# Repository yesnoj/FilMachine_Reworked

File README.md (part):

# FilMachine — Automated Film Development Machine

FilMachine is an automated film processing machine designed for photographic film development. It handles the entire process: chemical baths, water rinses, temperature regulation, and motor-driven film agitation — all controlled through a 4.3" color touchscreen display.

The project includes a **desktop simulator** (SDL2 + LVGL) that reproduces the full touchscreen UI on macOS/Linux (a Windows build is produced by CI), enabling rapid development and testing without physical hardware, plus an **automated test suite** (19 suites). A **Flutter companion app** connects via WebSocket and provides full remote control from any mobile device on the same network.

The interface is **bilingual (English / Italiano)** — selectable from Settings, applied with an automatic reboot — and every boot writes a **diagnostic log to the SD card** (`/log/boot_NNNN.txt`), including the crash summary of the previous run when the firmware panicked.

The repository also holds the mechanical side of the project: the 3D-printed **film reel auto-loader** (bench prototype v1, for 135 and 120 film) — see [Film Reel Auto-Loader](#film-reel-auto-loader-3d-printed-prototype).

---

## Table of Contents

1. [What is FilMachine?](#what-is-filmachine)
2. [Project Architecture](#project-architecture)
3. [Directory Structure](#directory-structure)
4. [Building the Project](#building-the-project)
5. [Running the Simulator](#running-the-simulator)
6. [Running the Tests](#running-the-tests)
7. [WebSocket Server & Remote Control](#websocket-server--remote-control)
8. [Flutter Companion App](#flutter-companion-app)
9. [User Interface Guide](#user-interface-guide)
10. [Firmware Update (OTA)](#firmware-update-ota)
11. [Hardware Specifications](#hardware-specifications)
12. [Bill of Materials (Components)](#bill-of-materials-components)
13. [Film Reel Auto-Loader (3D-Printed Prototype)](#film-reel-auto-loader-3d-printed-prototype)
14. [Diagnostics & Bring-up Page](#diagnostics--bring-up-page)
15. [Build-time Switches](#build-time-switches)
16. [Configuration & Persistence](#configuration--persistence)
17. [Language / Localization](#language--localization)
18. [SD Boot & Crash Log](#sd-boot--crash-log)
19. [Typical Workflows](#typical-workflows)
20. [Developer Quick Reference](#developer-quick-reference)
21. [Authors](#authors)

---

## What is FilMachine?

FilMachine takes the guesswork out of developing photographic film at home or in a small lab. Instead of manually timing each step, pouring chemicals by hand, and constantly checking the thermometer, FilMachine automates everything. You load your film in the developing tank, select a process, and press Start. The machine takes care of the rest: filling the right chemical at the right time, keeping the temperature stable, rotating the film at the correct speed, rinsing between steps, and alerting you when the process is complete.

It supports both **color negative** (C41, E6) and **black & white** film development workflows, with full customization of every parameter.

---

## Project Architecture

The project has a **dual-target build system** that produces ESP32-P4 firmware or a native desktop application from the same codebase. The only supported hardware board is the **Guition JC4880P433** (ESP32-P4).

### Technology Stack

| Layer | Firmware (ESP32-P4) | Simulator (macOS/Linux) |
|-------|-------------------|------------------------|
| **UI Library** | LVGL 9.5.0 | LVGL 9.5.0 (identical) |
| **Display** | ST7701S 480×800 MIPI-DSI → landscape 800×480 via PPA | SDL2 window (800×480) |
| **Touch Input** | GT911 (physical 480×800 → remapped to 800×480) | SDL2 mouse events |
| **Storage** | FatFS on MicroSD (SDMMC 4-bit, ~40 MB/s) | POSIX file I/O (sd/ directory) |
| **RTOS** | FreeRTOS (ESP-IDF) | Stub (queues work, tasks are no-ops) |
| **2D Acceleration** | PPA hardware engine (rotate, scale, blend, fill) | — |
| **Audio** | ES8311 codec via I2S + power amplifier | — |
| **Temp Sensors** | DS18B20 OneWire | Simulated (20°C ambient, heater model) |
| **Motor/Pump** | DBH-12V dual H-bridge (motor ch.A + pump ch.B) + MCP23017 solenoid driver | printf stubs |
| **OTA Updates** | esp_ota_ops + esp_http_server | Simulated (progress timer) |
| **Build Tool** | ESP-IDF (`idf.py`) | CMake + Make |
| **Sensors** | Flow meter, water level, hall effect | Simulated |
| **Compiler** | riscv32-esp-elf-gcc | Native cc/gcc/clang |

### How the Simulator Works

The simulator replaces all hardware-specific code with a **stub layer** that provides compatible implementations:

- **FatFS stubs** map firmware paths (e.g., `/FilMachine.json`) to files inside an `sd/` subdirectory of the directory the simulator is launched from, so read/write operations work transparently.
- **FreeRTOS stubs** provide working queue implementations (xQueueCreate, xQueueSend, xQueueReceive) using simple circular buffers. Task creation is a no-op since there are no real threads — instead, the main loop drains the system queue every frame.
- **Hardware stubs** (GPIO, I2C, SPI, solenoid driver, motor, temperature) are either no-ops or printf-based logging functions. Temperature readings come from a simple thermal model that simulates heating/cooling.
- **OTA stubs** simulate the firmware update flow with a progress timer (0→100%) and fake IP address, allowing full UI testing without real hardware.
- **LVGL's SDL2 driver** provides the display backend and mouse input, which simulates the capacitive touchscreen.

The key architectural principle is that **all UI code is shared 1:1** between firmware and simulator. Pages, elements, event handlers, and business logic are identical — only the hardware abstraction layer changes.

---

## Directory Structure

```
FilMachine_Reworked/
│
├── main/                          # Core source (shared with ESP32 firmware)
│   ├── include/
│   │   └── FilMachine.h           #   Main header — all structs, enums, constants, prototypes
│   ├── FilMachine.c               #   ESP32 entry point — board-conditional display/touch init
│   ├── accessories.c              #   Utilities — linked lists, deep copy, config I/O, keyboard
│   ├── lang.c                     #   EN/IT string table (generated by scripts/gen_lang.py)
│   ├── sd_log.c                   #   Boot/crash logger on SD (/log/boot_NNNN.txt, firmware only)
│   ├── mini_json.c                #   Dependency-free JSON parser for the config file
│   ├── ota_update.c               #   OTA firmware update (SD card + Wi-Fi web server)
│   ├── ws_server.c                #   WebSocket server for Flutter companion app
│   ├── film_loader.c              #   Film loading cycle (wind, stall detect, cut, tail) — Tools → Load film
│   └── ui_profile.c               #   Centralized UI layout constants (800×480)
│
├── c_pages/                       # UI pages (screens)
│   ├── page_splash.c              #   Splash screen — standard, random, and custom modes with
│   │                              #     10 palettes, 6 shape styles, 9 title fonts, PRNG engine
│   ├── page_menu.c                #   Tab bar navigation (Processes / Settings / Tools)
│   ├── page_processes.c           #   Process list with filtering
│   ├── page_processDetail.c       #   Process creation & editing
│   ├── page_stepDetail.c          #   Step creation & editing with validation
│   ├── page_settings.c            #   Machine settings, grouped in sections (process, rotation, liquids, display, system)
│   ├── page_tools.c               #   Maintenance tools, import/export, statistics, OTA
│   ├── page_checkup.c             #   Process execution — the most complex page
│   └── page_debug.c               #   Hidden diagnostics / bring-up page (live sensors, output tests)
│
├── c_elements/                    # Reusable UI components
│   ├── element_process.c          #   Process list item (drag, delete, duplicate)
│   ├── element_step.c             #   Step list item (swipe gestures, edit/delete)
│   ├── element_filterPopup.c      #   Filter dialog (name, type, preferred)
│   ├── element_messagePopup.c     #   Generic confirmation/alert popups
│   ├── element_rollerPopup.c      #   Numeric selector (roller) widget
│   ├── element_calibPopup.c       #   Dual temperature calibration popup (bath + chemistry offsets)
│   ├── element_speedPopup.c       #   Pump / motor speed tuning popup with live test
│   ├── element_fillPopup.c        #   Maintenance "Fill bath" popup (auto-stop on level, flow or timeout)
│   ├── element_loadPopup.c        #   Film loading popup (135/120, progress, Cut now, blade test)
│   ├── element_cleanPopup.c       #   Cleaning process UI with timer
│   ├── element_drainPopup.c       #   Drain process UI with animated tank bars
│   ├── element_splashPopup.c      #   Splash screen config popup with live preview
│   ├── element_selfcheckPopup.c   #   Self-check diagnostic wizard (8-phase hardware test)
│   ├── element_otaWifiPopup.c     #   Wi-Fi OTA update popup (IP + PIN + progress)
│   └── element_wifiPopup.c       #   Wi-Fi connection popup (scan, connect, status)
│
├── c_fonts/                       # Custom icon fonts (7 sizes: 15/20/30/40/50/60/100px)
│   │                              #   + 8 custom splash title fonts (48px) + Montserrat 64
├── drivers/                       # Custom peripheral drivers (ESP-IDF compatible)
│   ├── include/                   #   Driver headers (mcp23017.h, ds18b20.h, sensors.h, audio.h, servo.h)
│   ├── mcp23017.c                 #   I2C 16-bit I/O expander (Adafruit solenoid driver)
│   ├── ds18b20.c                  #   OneWire temperature sensor (shared bus)
│   ├── audio.c                    #   ES8311 codec bring-up + tone/volume (board only)
│   ├── servo.c                    #   Cutter servo, LEDC 50 Hz PWM on GPIO 28 (board only)
│   └── sensors.c                  #   Flow meter, water level, hall effect sensors (+ reel pulse counter)
│
├── components/                    # ESP32-P4 specific hardware drivers
│   ├── st7701_lcd/                #   ST7701S MIPI-DSI LCD driver (480×800)
│   ├── ppa_engine/                #   PPA hardware 2D accelerator (rotate, scale, fill, blend)
│   ├── driver/                    #   ESP-IDF driver compatibility shims
│   └── espressif__esp_lcd_touch/  #   Touch panel abstraction layer
│
├── src/
│   └── main.c                     # Simulator entry point (SDL2 display, main loop,
│                                  #   demo data generator, system queue drain)
│
├── stub/                          # Hardware abstraction for simulator
│   ├── esp_stubs.h/c              #   ESP32 GPIO, timer, heap stubs
│   ├── fatfs_stubs.h/c            #   FatFS → POSIX filesystem mapping
│   ├── freertos_stubs.h/c         #   Queue stubs (circular buffer), task stubs (no-op)
│   ├── driver/                    #   GPIO, I2C, LEDC, SDMMC driver stubs
│   └── (redirect headers)         #   Thin #include wrappers for ESP-IDF compatibility
│
├── tests/                         # Automated test suite
│   ├── test_runner.h/c            #   Test framework & entry point
│   ├── test_helpers.c             #   Touch input simulation
│   ├── test_navigation.c          #   Splash, menu, tab switching
│   ├── test_processes.c           #   Process list display & creation
│   ├── test_process_crud.c        #   Process create/read/update/delete
│   ├── test_steps.c               #   Step creation, swipe, deletion
│   ├── test_step_crud.c           #   Step lifecycle
│   ├── test_execution.c           #   Process checkup execution flow
│   ├── test_persistence.c         #   Config save/load/restore
│   ├── test_settings.c            #   Settings UI & validation
│   ├── test_filter.c              #   Filter logic
│   ├── test_tools.c               #   Maintenance tools
│   ├── test_edge_cases.c          #   Boundary conditions & error paths
│   ├── test_utilities.c           #   Helper function tests
│   ├── test_ota.c                 #   OTA update UI & Wi-Fi popup tests
│   ├── test_websocket.c           #   WebSocket command tests
│   ├── test_new_settings.c        #   Extended settings tests
│   ├── test_selfcheck.c           #   Self-check wizard tests
│   ├── test_live_sync.c           #   Live sync integration tests
│   ├── test_ui_profile.c          #   UI profile validation & sensor stubs
│   ├── test_film_loader.c         #   Film loader state machine, safety checks, popup
│   ├── test_maintenance_remote.c  #   Drain / Clean / Export driven by WebSocket commands
│   └── test_destroy_and_lifecycle.c # Memory cleanup & object destruction
│
├── lvgl/                          # LVGL 9.5.0 library (auto-cloned on first build, gitignored)
├── lvgl_config/
│   └── lv_conf.h                  # LVGL configuration (RGB565, C-library malloc as on the board, dark theme)
│
├── boards/                        # Board-specific hardware definitions
│   ├── board.h                    #   Board selector (includes correct board header)
│   ├── board_jc4880p433.h         #   JC4880P433 pin assignments, peripherals, H-bridge config
│   └── board_simulator.h          #   Simulator stubs (matching pin constants)
│
├── scripts/
│   ├── genFilMachineCFG.py        # SD config generator (FilMachine.json with realistic film recipes)
│   ├── gen_lang.py                # EN/IT string table generator (holds the Italian dictionary)
│   └── bump_version.sh            # Increments the BUILD field of version.txt
│
├── hardware/
│   └── FilMachine_Breakout_v1/    # KiCad project + BOM: breakout board for the Expand IO header
│
├── 3D_Models/
│   └── FilMachine_caricatore_v1/  # 3D-printed film reel auto-loader: STEP, STL, previews,
│                                  #   CadQuery source and its own README (in Italian)
│
├── docs/
│   └── hardware_architecture.svg  # System architecture diagram (shown under Hardware Specifications)
├── tools/
│   └── lvgl_splash_generator.jsx  # Splash-screen generator (React component that emits LVGL C code)
├── data/                          # Sample SD config files (FilMachine.json + legacy .cfg), not used by the build
├── .github/workflows/
│   └── windows-sim.yml            # CI: builds the simulator for Windows (MSYS2/MinGW)
│
├── CMakeLists.txt                 # Dual-target build (ESP-IDF P4 + simulator/tests)
├── version.txt                    # Firmware version, MAJOR.MINOR.PATCH.BUILD (single source of truth)
├── partitions.csv                 # Custom OTA partition table (16 MB flash)
├── sdkconfig.defaults             # ESP-IDF shared defaults
├── sdkconfig.defaults.esp32p4     # ESP-IDF defaults for ESP32-P4 target
├── flash_p4.sh                    # All-in-one build + flash + monitor for the ESP32-P4 board (macOS)
├── ui_debug_registry.inc          # Widget-name registry for the simulator's F2 debug overlay
├── COMMANDS.md                    # Quick command reference (in Italian)
├── AUDIT_REPORT.md                # Firmware/app audit of 6 July 2026 (firmware v0.0.0.50)
├── FilMachine_Custom_PCB_BOM.xlsx # Design worksheet for a custom PCB: BOM, pin maps, power budget (in Italian)
├── DistintaComponenti.xlsx        # Parts list with specs, quantities, prices and links (in Italian)
├── MDC_db.csv                     # Film/developer development-time table (9,142 rows; not read by the firmware yet)
├── setup.sh                       # Legacy: one-off script that built the old Simulator_v2 folder (not needed)
└── flash.sh                       # Legacy: ESP32-S3 flash through the old FilMachine_Pete repo (not for the P4)
```

---

## Building the Project

### Prerequisites

**macOS:**
```bash
brew install cmake sdl2 pkg-config
```

**Ubuntu / Debian:**
```bash
sudo apt install cmake libsdl2-dev pkg-config build-essential
```

LVGL v9.5.0 is automatically cloned from GitHub on the first build if not present (the firmware pulls the same version through the ESP-IDF component manager, `lvgl/lvgl ~9.5.0`).

**Windows:** there is no local recipe; the GitHub Actions workflow `.github/workflows/windows-sim.yml` builds `filmachine_sim.exe` with MSYS2/MinGW on every push to `main` that changes more than the documentation (or on demand from the Actions tab) and uploads it — with its runtime DLLs and a freshly generated `sd/` config — as the `filmachine-sim-windows` artifact.

### Build the Simulator

```bash
mkdir -p build800 && cd build800
cmake ..
make filmachine_sim
```

The simulator opens an 800×480 window matching the JC4880P433 physical panel in landscape orientation.

### Build the Tests

```bash
mkdir -p build800 && cd build800
cmake ..
make filmachine_test
./filmachine_test
```

### Build the Firmware

Requires the [ESP-IDF](https://docs.espressif.com/projects/esp-idf/en/latest/) toolchain (**v5.5.x** or later) installed and configured.

**Important:** run `idf.py` from the **project root**, not from `build800/`.

```bash
cd FilMachine_Reworked
. $HOME/esp/esp-idf-v5.5/export.sh     # Must be ESP-IDF 5.5.x or later

# First-time setup: set target to esp32p4 (creates sdkconfig from defaults)
idf.py set-target esp32p4

# Build — board is auto-detected from IDF_TARGET
idf.py build
```

The `main/CMakeLists.txt` automatically sets `-DBOARD_JC4880P433`. No manual `-DCMAKE_C_FLAGS` flag is needed (passing `-D CMAKE_C_FLAGS="-DBOARD_JC4880P433"` is harmless but redundant).

> **See [`COMMANDS.md`](COMMANDS.md)** for the canonical quick reference: simulator + board build, flash/monitor, generating and copying the SD config, version bumping and cleanup.

#### Flash and monitor

The firmware binary is produced at `build/FilMachine.bin`. To flash it directly to a connected board:

```bash
idf.py flash
```

Or use the all-in-one helper (written for macOS), which sets the target if needed, patches `sdkconfig` for the P4 board, increments the build number in `version.txt`, builds, looks for the serial port, flashes and opens the monitor:
```bash
./flash_p4.sh
```

> `flash.sh` and `setup.sh` are leftovers of the earlier ESP32-S3 workflow (they copy sources between the old `FilMachine_Simulator_v2` folder and the `FilMachine_Pete` repository). They are not used for the ESP32-P4 and can be ignored.

**P4 note:** the bootloader offset on ESP32-P4 is `0x2000` (different from ESP32-S3's `0x0`). This is handled automatically by `idf.py` when the target is set correctly.

To check the firmware size (useful for verifying OTA partition fit):
```bash
idf.py size
```

---

## Running the Simulator

### Simulator UI debug overlay

The simulator includes a built-in UI inspection mode to speed up layout tuning.

- Press **F2** to enable or disable the overlay.
- When enabled, moving the mouse over the UI shows:
  - the resolved component name when available (for example `gui.page.processes.newProcessButton`)
  - the object position (`x`, `y`)
  - the object size (`w`, `h`)
- While the overlay is enabled, **right click** dumps the hovered object to the terminal/console.

This is especially useful when adjusting coordinates inside `ui_profile.c`, because you can identify the exact widget and immediately see its current geometry in the simulator.

```bash
cd build800
./filmachine_sim
```

The simulator opens an 800×480 window that reproduces the exact touchscreen interface. Use the mouse to simulate touch input (click = tap, click-drag = swipe/scroll).

### What works in the simulator

- Full UI navigation (all pages, popups, dialogs)
- Splash screen with live preview popup, 10 palettes, 6 shape styles, 9 custom fonts
- Process creation, editing, duplication, deletion
- Step management with swipe gestures
- Settings with slider/switch/radio controls
- Filter and search functionality
- Configuration save/load (reads/writes `sd/FilMachine.json`)
- Export/Import (backup to `sd/FilMachine_Backup.json`)
- Drain machine with animated tank-level bars and relay management
- Empty chemistry (machine v7): C1, C2 or C3 into its recovery bottle through the pump and the recovery outlet, line washed before and after, with a source → tank → bottle animation
- Clean machine with per-container rinse cycles and arc progress
- Self-check diagnostic wizard with 8-phase hardware test simulation (temp sensors, pump, heater, valves, containers, motor)
- OTA update UI (SD card check + Wi-Fi popup with simulated IP/PIN/progress)
- Simulated temperature readings with heater model and calibration offset
- Persistent alarm sound (SDL audio 880Hz beep, repeats every 10s until dismissed)
- Drain/fill overlap processing (adjusts step timing based on overlap percentage)
- Machine statistics persistence (saved in config file, survives restart)
- Temperature sensor calibration (Tune button calculates and applies offset)
- Console logging of all system actions (`[SIM] sysAction: ...`)
- WebSocket server on port 81 for Flutter companion app remote control
- Full remote process start, stop, and checkup advance via WebSocket
- Remote CRUD for processes and steps (create, edit, delete from Flutter)

### What is simulated (no real hardware)

- Temperature sensors return simulated values (20°C ambient, gradual heating/cooling)
- Motor control outputs to console only
- Relay switching outputs to console only
- OTA writes to a fake partition (progress simulated, no actual flash)
- Wi-Fi connection is simulated (fake IP 192.168.1.42, no real server)
- Reboot is a no-op (prints message)

### Generating sample data

To generate realistic film development recipes:

```bash
python3 scripts/genFilMachineCFG.py --realistic --output build800/sd/
```

This creates config files with authentic C41, E6, and B&W development processes.

---

## Running the Tests

```bash
cd build800
./filmachine_test
```

Results are displayed in the terminal and saved to `test_results/test_results_YYYYMMDD_HHMMSS.txt`.

### Test Suites

| Suite | Description |
|-------|-------------|
| **Navigation** | Splash screen, menu display, tab switching |
| **Processes** | Process list rendering, creation UI |
| **Process CRUD** | Full create/read/update/delete lifecycle |
| **Steps** | Step creation, swipe gestures, deletion |
| **Step CRUD** | Step lifecycle with validation |
| **Execution** | Process checkup and execution flow |
| **Persistence** | Config save → reload → verify all fields, stats persistence, calibration offset |
| **Settings** | Settings UI, default values, slider/switch behavior, calibration, alarm |
| **Filter** | Filter by name, film type, preferred flag |
| **Tools** | Cleaning, draining, statistics display, timer pause/resume, alarm functions |
| **Edge Cases** | Boundary conditions, max limits, error recovery |
| **Utilities** | Helper functions, linked list operations, drain/fill overlap calculation |
| **UI Profile & Sensors** | Profile values match original, popup dimensions, font pointers, sensor stubs, board constants |
| **OTA** | OTA update UI, Wi-Fi popup PIN generation, progress popup |
| **WebSocket** | WebSocket command handling, async LVGL dispatch |
| **New Settings** | Extended settings validation |
| **Self-check** | Self-check diagnostic wizard phases |
| **LiveSync** | Live sync between WebSocket state and LVGL UI |
| **Destroy & Lifecycle** | Memory cleanup, object destruction |
| **Film loader** | Loading cycle 135/120, early stall / no spin / too long errors, Cut now, Stop, blade test, popup from the app |
| **Maintenance from the app** | Drain and Clean started, stopped and closed by WebSocket commands (popups on the display, state fields), only the selected containers cleaned, one tool at a time, no process while one runs, Export queued with its result in the state |

The persistence tests verify that every field (process name, temperature, tolerance, film type, preferred flag, step names, durations, types, sources, discard flags) survives a full save-and-reload cycle.

**Repeatable runs.** Every run starts from the same data: the runner generates three test processes with the default settings and rewrites `sd/FilMachine.json` in the run directory, so a run never depends on what the previous one saved (steps used to pile up on the first process until the 30-step limit made the step tests fail). `FM_TEST_ONLY=<suite>,<suite>` runs only some suites (names after `test_suite_`, e.g. `FM_TEST_ONLY=navigation,tools`).

**Timers run on real time.** The SDL display makes LVGL read the real clock, so `test_pump()` processes events but does not advance LVGL timers; tests that wait for a 1 s timer sleep (see `pump_real()` in `test_maintenance_remote.c`).

**Memory.** The simulator and the tests use the C-library `malloc` for LVGL, like the board. With LVGL's own 256 KB pool the heap fragmented after a few suites, an allocation failed and LVGL's malloc assert spun forever, which looked like random hangs in the step tests. To check memory errors, build the runner with `-fsanitize=address`: AddressSanitizer then sees LVGL's allocations too.

---

## WebSocket Server & Remote Control

The simulator and firmware include a built-in WebSocket server (`ws_server.c`) that enables remote control from the Flutter companion app or any WebSocket client. The server starts automatically and listens on **port 81** at path `/ws`.

### Supported Commands

All commands use JSON format: `{"cmd":"command_name", ...params}`.

| Command | Parameters | Description |
|---------|-----------|-------------|
| `get_state` | — | Returns full machine state (settings, runtime, temperatures, progress, alarms, maintenance fill, film loader, drain, clean and export status) |
| `get_processes` | — | Returns complete process list with steps, indexed for remote referencing |
| `start_process` | `index` | Start a process by list index; initializes checkup and begins execution |
| `checkup_advance` | — | Advance to next checkup phase (Setup → Fill → Temp → Check → Processing) |
| `stop_now` | — | Immediately halt the running process and drain |
| `stop_after` | — | Stop after the current step completes |
| `close_process` | — | Close a finished/stopped process and free checkup resources |
| `create_process` | `name, temp, tolerance, filmType, tempControlled, preferred` | Create a new process |
| `edit_process` | `index, name, temp, tolerance, filmType, tempControlled, preferred` | Edit an existing process |
| `delete_process` | `index` | Delete a process |
| `add_step` | `processIndex, name, mins, secs, type, source, discard` | Add a step to a process |
| `edit_step` | `processIndex, stepIndex, name, mins, secs, type, source, discard` | Edit a step |
| `delete_step` | `processIndex, stepIndex` | Delete a step |
| `reorder_step` | `processIndex, from, to` | Move a step within a process |
| `set_setting` | `key, value` | Update a machine setting (see key list below) |
| `reset_defaults` | — | Restore all settings to factory defaults |
| `wifi_scan` | — | Scan for Wi-Fi networks; results arrive via a `wifi_scan_results` event |
| `fill_start` / `fill_stop` | `target` (0 = water bath, 1 = chemistry) | Maintenance fill (self-calibrates the fill time; refused with `fill_rejected` while a process runs) |
| `tune_test` / `tune_set` / `tune_cancel` | `kind` (0 pump, 1 motor, 2 volume), `percent`, `on` | Live test, store or cancel a Tune value |
| `drain_start` / `drain_stop` / `drain_close` | — | Drain machine: start (no confirm page, the app asks), Stop, Close after the end (alarm off, popup closed). Refused with `drain_rejected` while a process or another maintenance tool runs |
| `recover_start` / `recover_stop` / `recover_close` | `container` (0 = C1, 1 = C2, 2 = C3) | Empty that chemistry into its recovery bottle (machine v7): wash the line, discard the head, transfer, wash again. Progress in `recoverToolState` (0 idle, 1 running, 2 stopping, 3 done, 4 stopped), `recoverToolPhase` (0..3), `recoverToolPct`, `recoverToolRemaining`, `recoverToolMovedMl`. Refused with `recover_rejected` while a process or another tool runs; a drain still finishing is waited for |
| `clean_start` | `mask` (bit0 C1, bit1 C2, bit2 C3), `cycles` (1–5), `drainWb` | Clean machine with these choices (shown on the display popup). Refused with `clean_rejected` (`processing`, `busy`, `no_container`) |
| `clean_stop` / `clean_close` | — | Clean: Stop (the container is pumped back first) / Close after the end |
| `export_config` | — | Export configuration and processes to the backup file on the SD card; the result arrives as `exportSeq` / `exportOk` in the state |
| `load_start` | `format` (0 = 135, 1 = 120) | Start loading the film onto the reel (refused with a `load_rejected` event while a process runs or a load is in progress) |
| `load_stop` | — | Stop the loading (motor off, blade back to rest) |
| `load_cut` | — | Cut now, without waiting for the reel to stop |
| `cutter_test` | `angle` (0–180) | Hold the cutter servo at that angle for a few seconds (setup) |
| `cutter_cycle` | — | One blade up/down cycle, motor off |

The `cleanTool*` state fields include `cleanToolProcessArc`, `cleanToolCycleArc` and `cleanToolPumpArc`: the values of the three arcs exactly as drawn on the display's Clean popup, so the app draws the same picture.

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
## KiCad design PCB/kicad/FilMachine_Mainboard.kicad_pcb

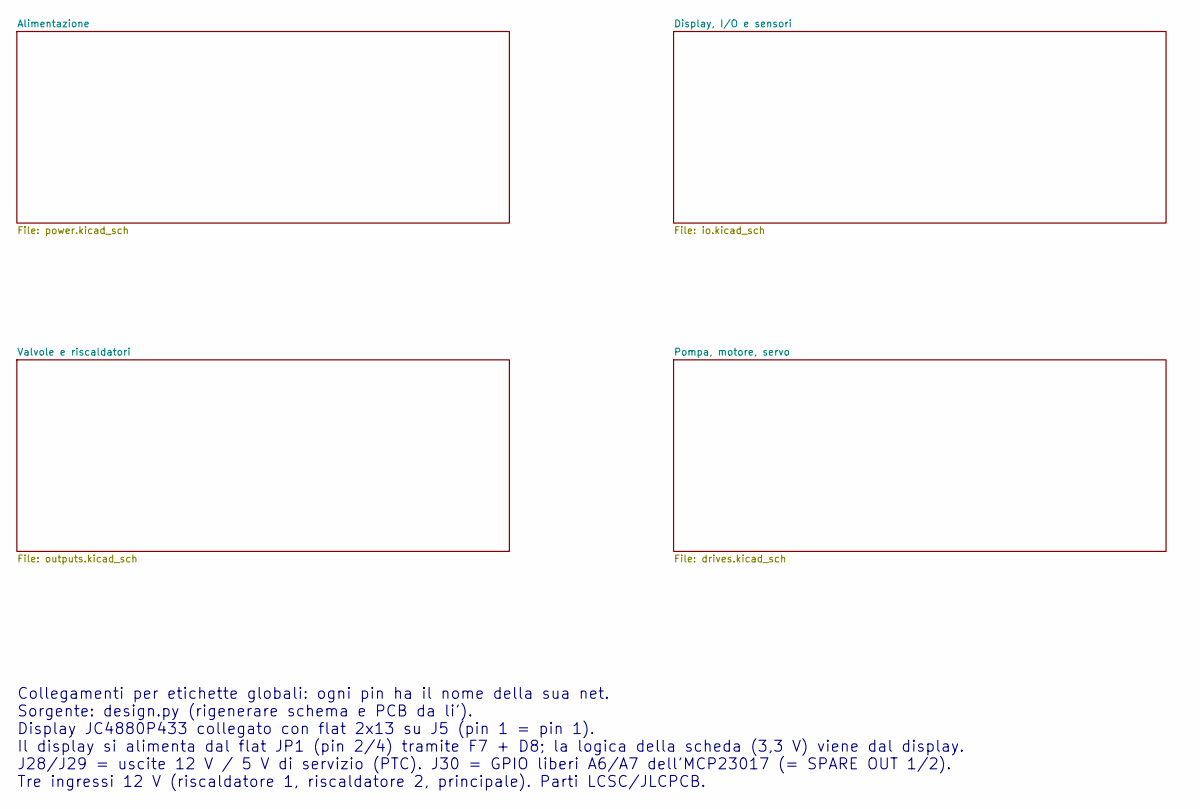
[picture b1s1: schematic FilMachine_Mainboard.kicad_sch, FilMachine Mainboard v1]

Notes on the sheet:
Collegamenti per etichette globali: ogni pin ha il nome della sua net. Sorgente: design.py (rigenerare schema e PCB da li'). Display JC4880P433 collegato con flat 2x13 su J5 (pin 1 = pin 1). Il display si alimenta dal flat JP1 (pin 2/4) tramite F7 + D8; la logica della scheda (3,3 V) viene dal disp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

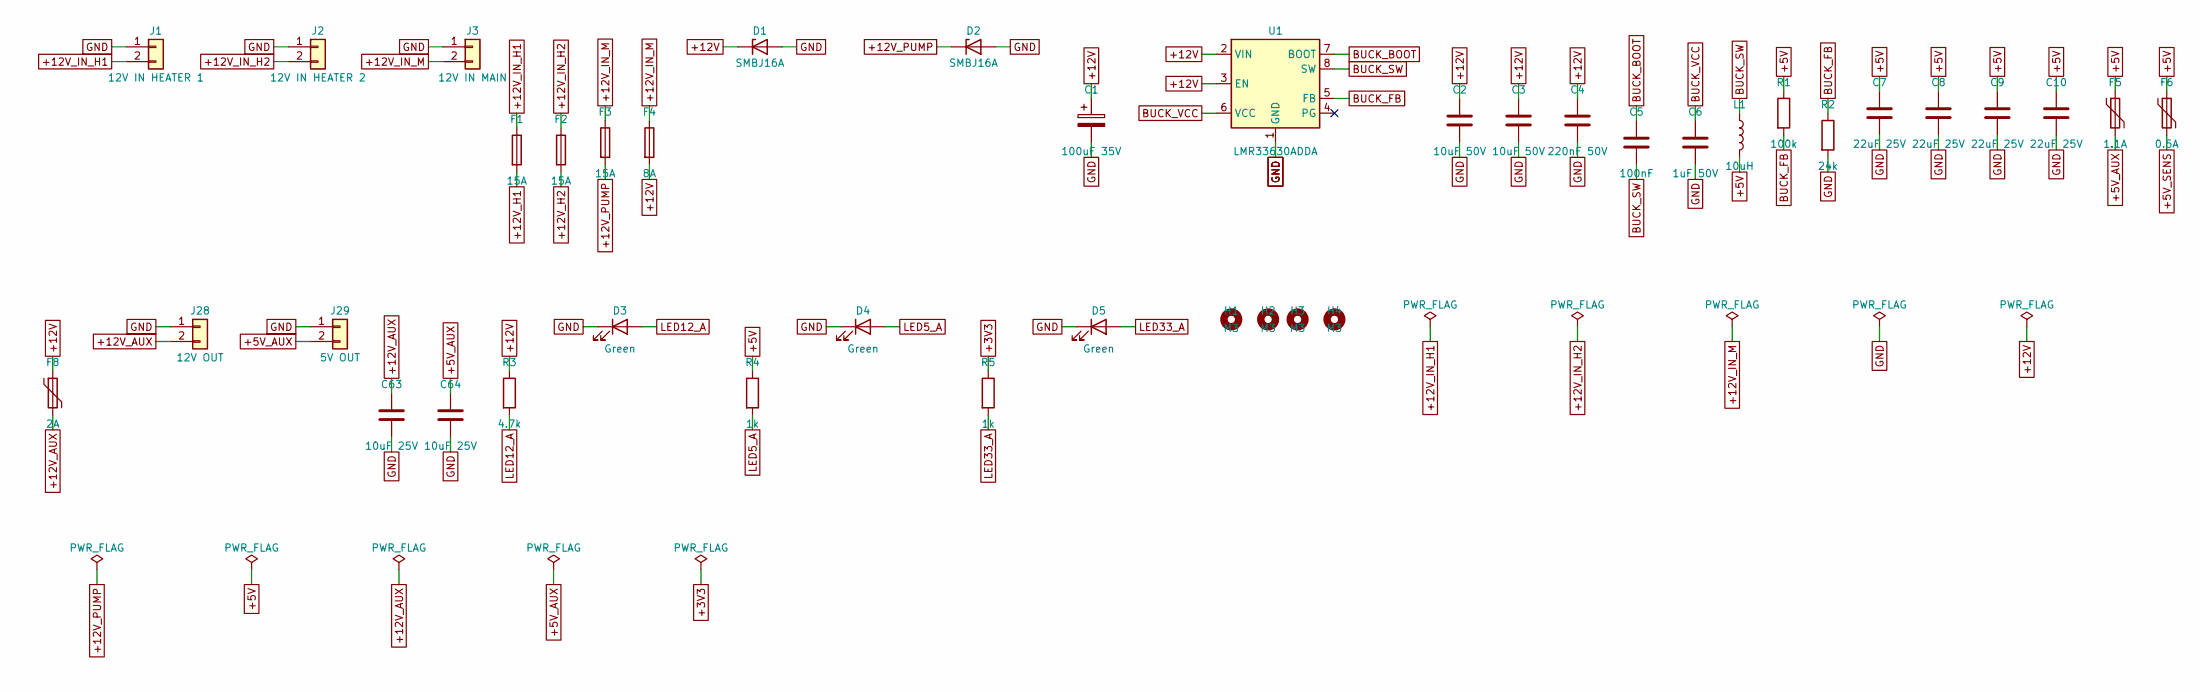
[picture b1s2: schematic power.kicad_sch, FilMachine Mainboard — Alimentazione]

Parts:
C1: 100uF 35V; CP_Radial_D6.3mm_P2.50mm; MPN ERS1VM101E12OT; LCSC C106694
C2, C3: 10uF 50V; C_1206_3216Metric; MPN MLCC 10uF 50V; LCSC C13585
C4: 220nF 50V; C_0805_2012Metric; MPN MLCC 220nF 50V; LCSC C5378
C5: 100nF; C_0603_1608Metric; MPN MLCC 100nF; LCSC C14663
C6: 1uF 50V; C_0603_1608Metric; MPN MLCC 1uF 50V; LCSC C15849
C7, C8, C9, C10: 22uF 25V; C_1206_3216Metric; MPN MLCC 22uF 25V; LCSC C12891
C63, C64: 10uF 25V; C_0805_2012Metric; MPN MLCC 10uF 25V; LCSC C15850
D1, D2: SMBJ16A; D_SMB; MPN SMBJ16A; LCSC C19077571
D3, D4, D5: Green; LED_0805_2012Metric; MPN KT-0805G; LCSC C2297
F1, F2, F3: 15A; FUSE_2410_SMD; MPN JFC2410-2150TS; LCSC C136393
F4: 8A; FUSE_2410_SMD; MPN JFC2410-1800TS; LCSC C136390
F5: 1.1A; Fuse_1812_4532Metric; MPN SMD1812B110TF/33; LCSC C269134
F6: 0.5A; Fuse_1206_3216Metric; MPN JK-nSMD050-30; LCSC C720075
F8: 2A; Fuse_1812_4532Metric; MPN BSMD1812-200-30V; LCSC C960026
H1, H2, H3, H4: M3; MountingHole_3.2mm_M3
J1: 12V IN HEATER 1; TB_WJ500V-5.08-2P; MPN WJ500V-5.08-2P; LCSC C8465
J2: 12V IN HEATER 2; TB_WJ500V-5.08-2P; MPN WJ500V-5.08-2P; LCSC C8465
J3: 12V IN MAIN; TB_WJ500V-5.08-2P; MPN WJ500V-5.08-2P; LCSC C8465
J28: 12V OUT; TB_DB301V-3.5-2P; MPN DB301V-3.5-2P-GN-S; LCSC C695629
J29: 5V OUT; TB_DB301V-3.5-2P; MPN DB301V-3.5-2P-GN-S; LCSC C695629
L1: 10uH; L_SLO0630H; MPN SLO0630H100MTT; LCSC C207842
R1: 100k; R_0603_1608Metric; MPN 0603 100k 1%; LCSC C25803
R2: 24k; R_0603_1608Metric; MPN 0603 24k 1%; LCSC C23352
R3: 4.7k; R_0603_1608Metric; MPN 0603 4.7k 1%; LCSC C23162
R4, R5: 1k; R_0603_1608Metric; MPN 0603 1k 1%; LCSC C21190
U1: LMR33630ADDA; TI_SO-PowerPAD-8_ThermalVias; MPN LMR33630ADDAR; LCSC C841384

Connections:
+3V3: R5.1; also elsewhere on the board
+5V: C7.1, C8.1, C9.1, C10.1, F5.1, F6.1, L1.2, R1.1, R4.1; also elsewhere on the board
+5V_AUX: C64.1, F5.2, J29.2; also elsewhere on the board
+5V_SENS: F6.2; also elsewhere on the board
+12V: C1.1, C2.1, C3.1, C4.1, D1.1 (K), F4.2, F8.1, R3.1, U1.2 (VIN), U1.3 (EN); also elsewhere on the board
+12V_AUX: C63.1, F8.2, J28.2
+12V_H1: F1.2; also elsewhere on the board
+12V_H2: F2.2; also elsewhere on the board
+12V_IN_H1: F1.1, J1.2
+12V_IN_H2: F2.1, J2.2
+12V_IN_M: F3.1, F4.1, J3.2
+12V_PUMP: D2.1 (K), F3.2; also elsewhere on the board
BUCK_BOOT: C5.1, U1.7 (BOOT)
BUCK_FB: R1.2, R2.1, U1.5 (FB)
BUCK_SW: C5.2, L1.1, U1.8 (SW)
BUCK_VCC: C6.1, U1.6 (VCC)
GND: C1.2, C2.2, C3.2, C4.2, C6.2, C7.2, C8.2, C9.2, C10.2, C63.2, C64.2, D1.2 (A), D2.2 (A), D3.1 (K), D4.1 (K), D5.1 (K), J1.1, J2.1, J3.1, J28.1, J29.1, R2.2, U1.1 (GND), U1.9 (GND); also elsewhere on the board
LED5_A: D4.2 (A), R4.2
LED12_A: D3.2 (A), R3.2
LED33_A: D5.2 (A), R5.2

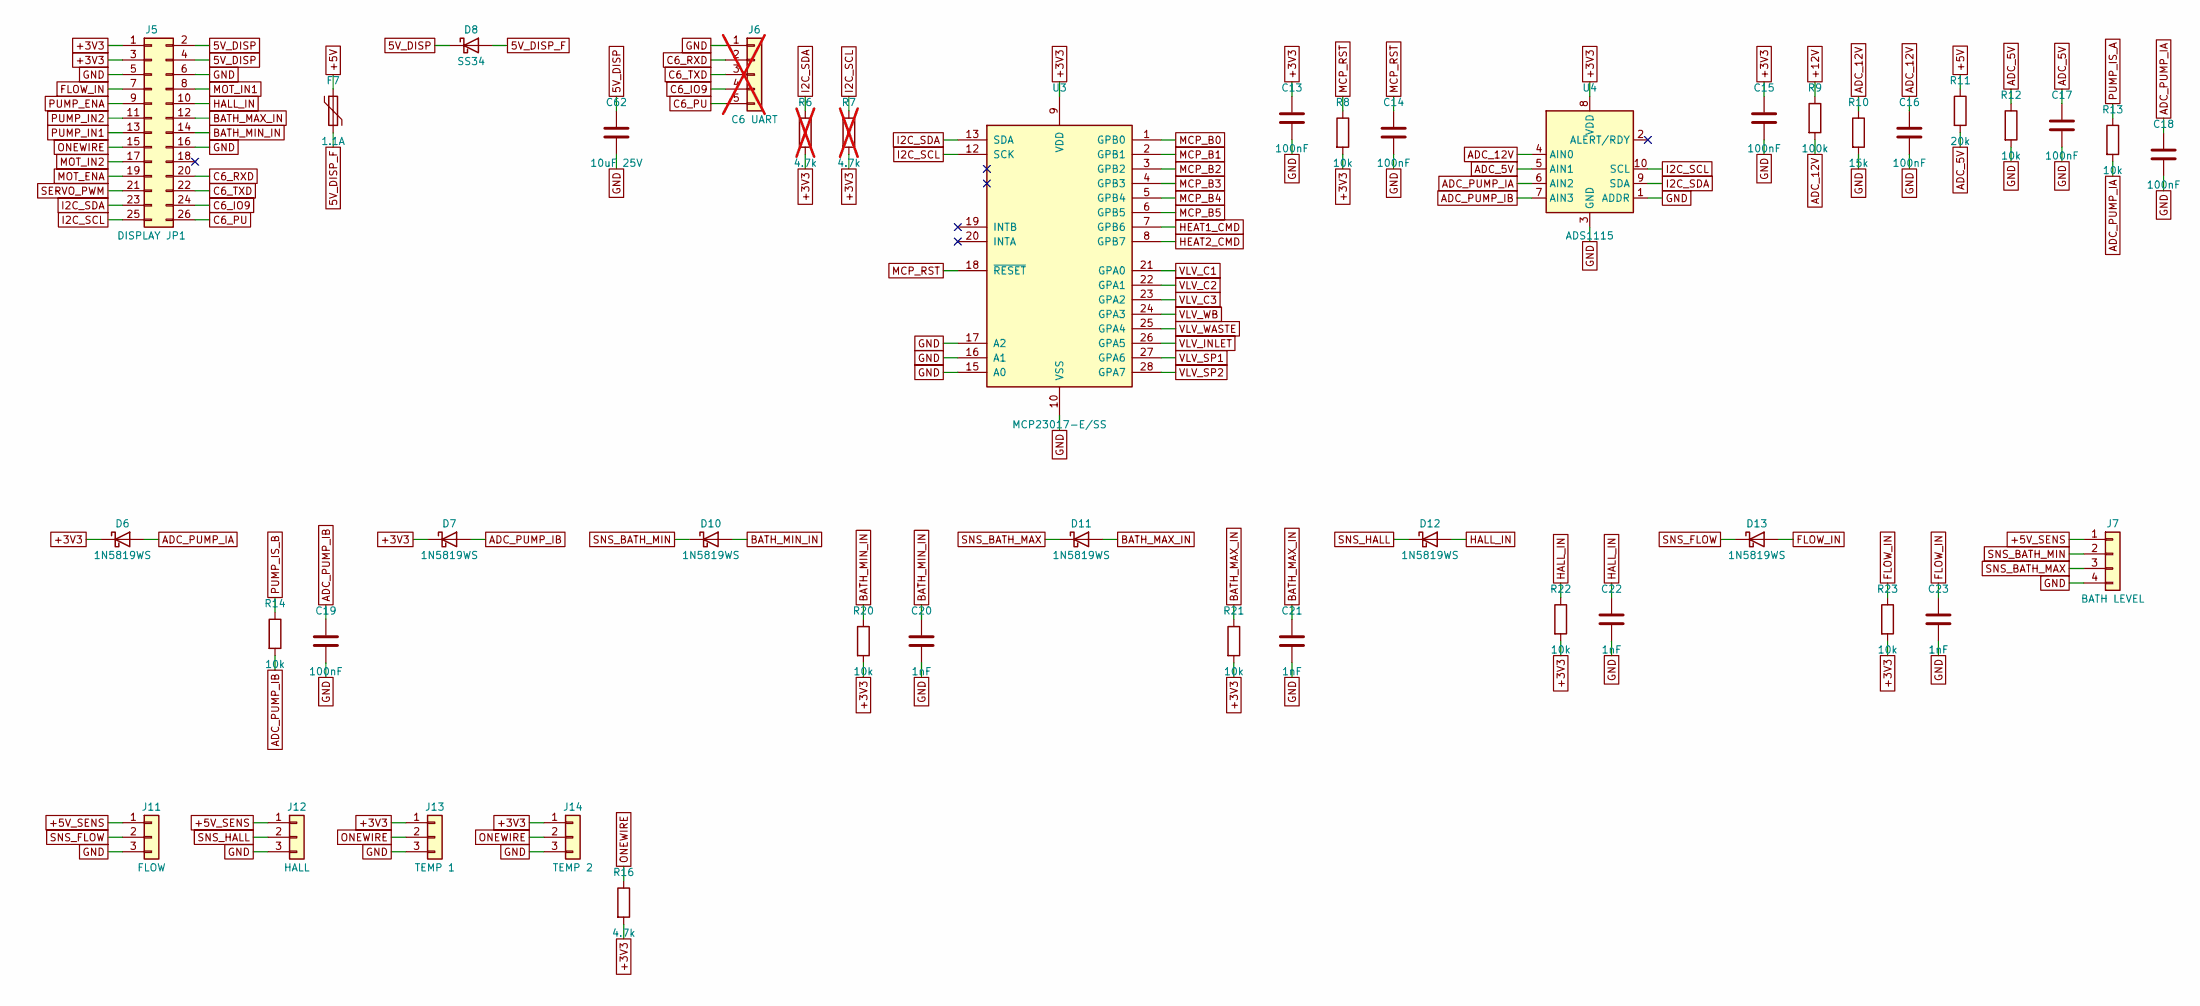
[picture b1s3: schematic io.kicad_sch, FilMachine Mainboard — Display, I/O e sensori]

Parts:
C13, C14, C15, C16, C17, C18, C19: 100nF; C_0603_1608Metric; MPN MLCC 100nF; LCSC C14663
C20, C21, C22, C23: 1nF; C_0603_1608Metric; MPN MLCC 1nF; LCSC C1588
C62: 10uF 25V; C_0805_2012Metric; MPN MLCC 10uF 25V; LCSC C15850
D6, D7, D10, D11, D12, D13: 1N5819WS; D_SOD-323; MPN 1N5819WS; LCSC C191023
D8: SS34; D_SMA; MPN SS34; LCSC C8678
F7: 1.1A; Fuse_1812_4532Metric; MPN SMD1812B110TF/33; LCSC C269134
J5: DISPLAY JP1; IDC-Header_2x13_P2.54mm_Horizontal; MPN DS1013-26RSiB-B-0; LCSC C7430326
J6: C6 UART; PinHeader_1x05_P2.54mm_Vertical; not fitted
J7: BATH LEVEL; JST_XH_B4B-XH-A_1x04_P2.50mm_Vertical; MPN XH-4A; LCSC C37815
J11: FLOW; JST_XH_B3B-XH-A_1x03_P2.50mm_Vertical; MPN XH-3A; LCSC C2316
J12: HALL; JST_XH_B3B-XH-A_1x03_P2.50mm_Vertical; MPN XH-3A; LCSC C2316
J13: TEMP 1; JST_XH_B3B-XH-A_1x03_P2.50mm_Vertical; MPN XH-3A; LCSC C2316
J14: TEMP 2; JST_XH_B3B-XH-A_1x03_P2.50mm_Vertical; MPN XH-3A; LCSC C2316
R6, R7: 4.7k; R_0603_1608Metric; MPN 0603 4.7k 1%; LCSC C23162; not fitted
R8, R12, R13, R14, R20, R21, R22, R23: 10k; R_0603_1608Metric; MPN 0603 10k 1%; LCSC C25804
R9: 100k; R_0603_1608Metric; MPN 0603 100k 1%; LCSC C25803
R10: 15k; R_0603_1608Metric; MPN 0603 15k 1%; LCSC C22809
R11: 20k; R_0603_1608Metric; MPN 0603 20k 1%; LCSC C4184
R16: 4.7k; R_0603_1608Metric; MPN 0603 4.7k 1%; LCSC C23162
U3: MCP23017-E/SS; SSOP-28_5.3x10.2mm_P0.65mm; MPN MCP23017T-E/SS; LCSC C558584
U4: ADS1115; VSSOP-10_3x3mm_P0.5mm; MPN ADS1115IDGSR; LCSC C37593

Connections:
5V_DISP: C62.1, D8.1 (K), J5.2, J5.4
5V_DISP_F: D8.2 (A), F7.2
+3V3: C13.1, C15.1, D6.1 (K), D7.1 (K), J5.1, J5.3, J13.1, J14.1, R6.2, R7.2, R8.2, R16.2, R20.2, R21.2, R22.2, R23.2, U3.9 (VDD), U4.8 (VDD); also elsewhere on the board
+5V: F7.1, R11.1; also elsewhere on the board
+5V_SENS: J7.1, J11.1, J12.1; also elsewhere on the board
+12V: R9.1; also elsewhere on the board
ADC_5V: C17.1, R11.2, R12.1, U4.5 (AIN1)
ADC_12V: C16.1, R9.2, R10.1, U4.4 (AIN0)
ADC_PUMP_IA: C18.1, D6.2 (A), R13.2, U4.6 (AIN2)
ADC_PUMP_IB: C19.1, D7.2 (A), R14.2, U4.7 (AIN3)
BATH_MAX_IN: C21.1, D11.2 (A), J5.12, R21.1
BATH_MIN_IN: C20.1, D10.2 (A), J5.14, R20.1
C6_IO9: J5.24, J6.4
C6_PU: J5.26, J6.5
C6_RXD: J5.20, J6.2
C6_TXD: J5.22, J6.3
FLOW_IN: C23.1, D13.2 (A), J5.7, R23.1
GND: C13.2, C14.2, C15.2, C16.2, C17.2, C18.2, C19.2, C20.2, C21.2, C22.2, C23.2, C62.2, J5.5, J5.6, J5.16, J6.1, J7.4, J11.3, J12.3, J13.3, J14.3, R10.2, R12.2, U3.10 (VSS), U3.15 (A0), U3.16 (A1), U3.17 (A2), U4.1 (ADDR), U4.3 (GND); also elsewhere on the board
HALL_IN: C22.1, D12.2 (A), J5.10, R22.1
HEAT1_CMD: U3.7 (GPB6); also elsewhere on the board
HEAT2_CMD: U3.8 (GPB7); also elsewhere on the board
I2C_SCL: J5.25, R7.1, U3.12 (SCK), U4.10 (SCL)
I2C_SDA: J5.23, R6.1, U3.13 (SDA), U4.9 (SDA)
MCP_B0: U3.1 (GPB0); also elsewhere on the board
MCP_B1: U3.2 (GPB1); also elsewhere on the board
MCP_B2: U3.3 (GPB2); also elsewhere on the board
MCP_B3: U3.4 (GPB3); also elsewhere on the board
MCP_B4: U3.5 (GPB4); also elsewhere on the board
MCP_B5: U3.6 (GPB5); also elsewhere on the board
MCP_RST: C14.1, R8.1, U3.18 (~RESET)
MOT_ENA: J5.19; also elsewhere on the board
MOT_IN1: J5.8; also elsewhere on the board
MOT_IN2: J5.17; also elsewhere on the board
ONEWIRE: J5.15, J13.2, J14.2, R16.1
PUMP_ENA: J5.9; also elsewhere on the board
PUMP_IN1: J5.13; also elsewhere on the board
PUMP_IN2: J5.11; also elsewhere on the board
PUMP_IS_A: R13.1; also elsewhere on the board
PUMP_IS_B: R14.1; also elsewhere on the board
SERVO_PWM: J5.21; also elsewhere on the board
SNS_BATH_MAX: D11.1 (K), J7.3
SNS_BATH_MIN: D10.1 (K), J7.2
SNS_FLOW: D13.1 (K), J11.2
SNS_HALL: D12.1 (K), J12.2
VLV_C1: U3.21 (GPA0); also elsewhere on the board
VLV_C2: U3.22 (GPA1); also elsewhere on the board
VLV_C3: U3.23 (GPA2); also elsewhere on the board
VLV_INLET: U3.26 (GPA5); also elsewhere on the board
VLV_SP1: U3.27 (GPA6); also elsewhere on the board
VLV_SP2: U3.28 (GPA7); also elsewhere on the board
VLV_WASTE: U3.25 (GPA4); also elsewhere on the board
VLV_WB: U3.24 (GPA3); also elsewhere on the board

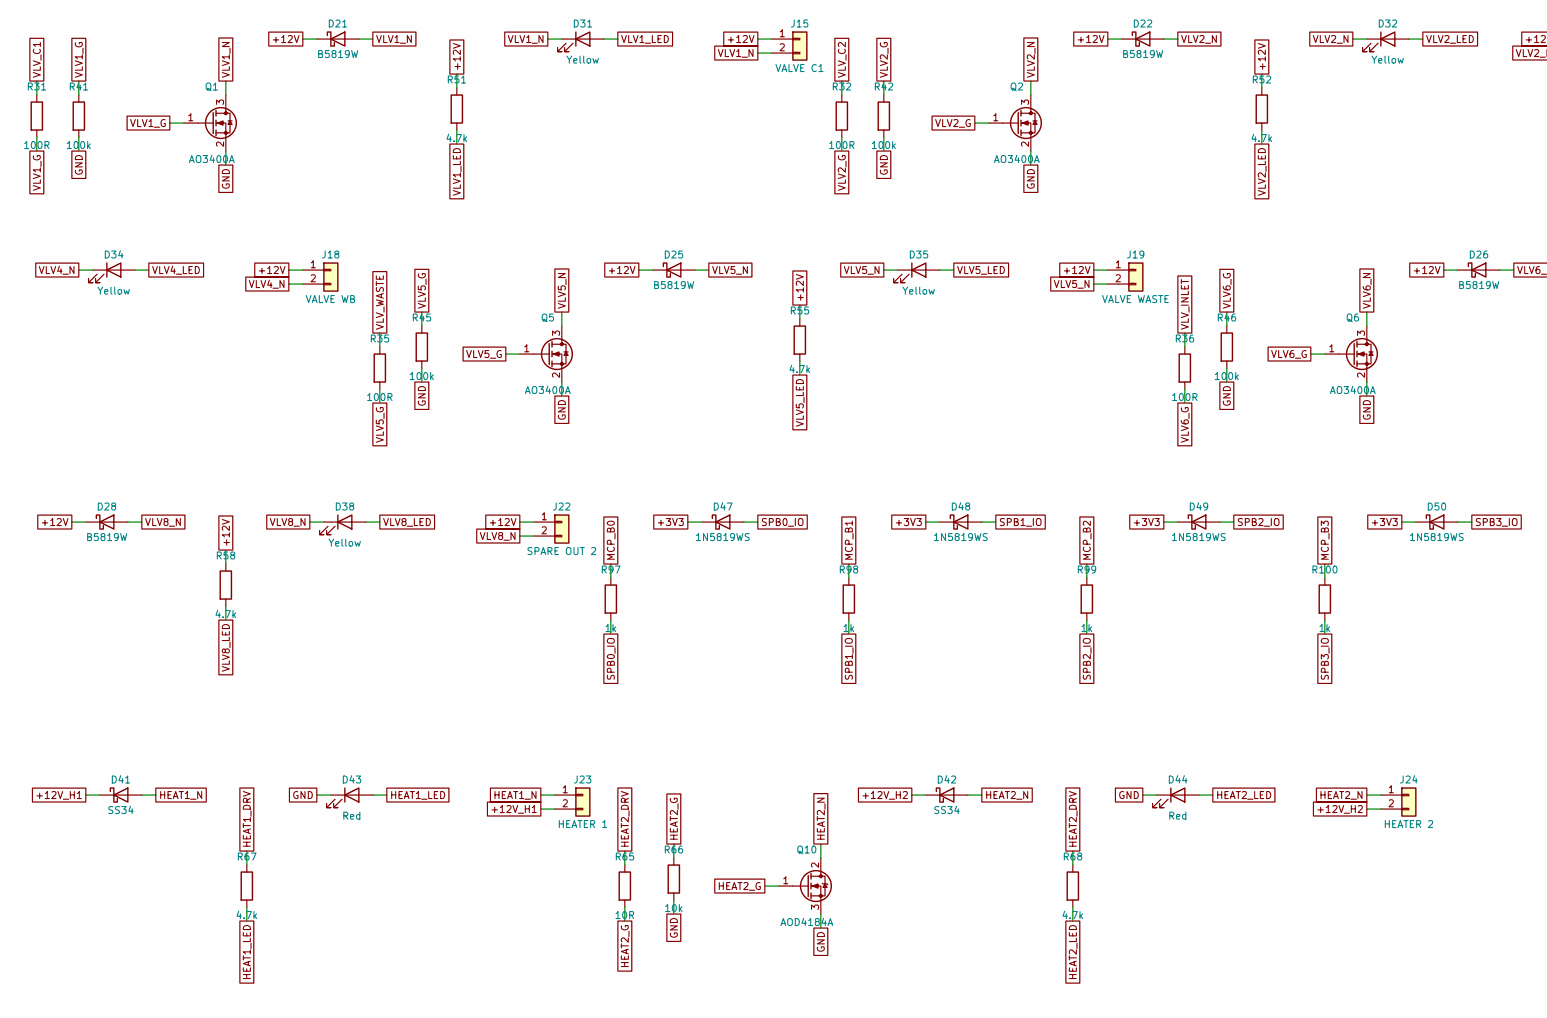
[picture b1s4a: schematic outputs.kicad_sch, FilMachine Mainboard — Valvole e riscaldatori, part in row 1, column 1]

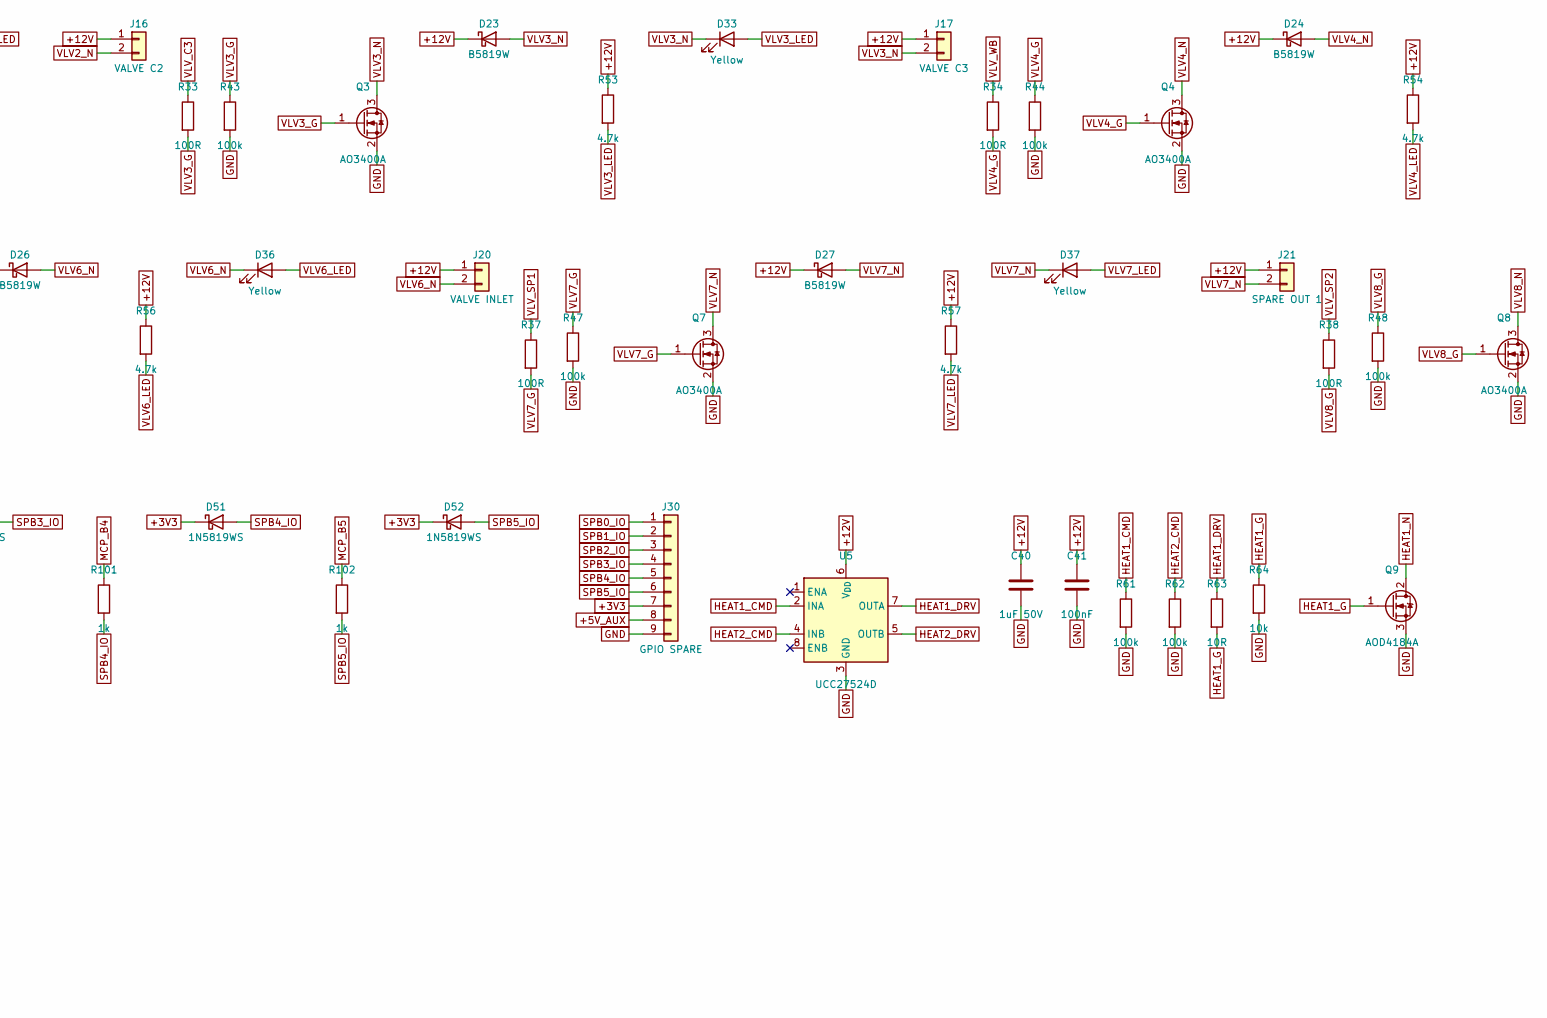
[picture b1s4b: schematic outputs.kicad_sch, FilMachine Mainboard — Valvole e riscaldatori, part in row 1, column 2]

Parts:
C40: 1uF 50V; C_0805_2012Metric; MPN MLCC 1uF 50V; LCSC C28323
C41: 100nF; C_0603_1608Metric; MPN MLCC 100nF; LCSC C14663
D21, D22, D23, D24, D25, D26, D27, D28: B5819W; D_SOD-123; MPN B5819W SL; LCSC C8598
D31, D32, D33, D34, D35, D36, D37, D38: Yellow; LED_0805_2012Metric; MPN KT-0805Y; LCSC C2296
D41, D42: SS34; D_SMA; MPN SS34; LCSC C8678
D43, D44: Red; LED_0603_1608Metric; MPN KT-0603R; LCSC C2286
D47, D48, D49, D50, D51, D52: 1N5819WS; D_SOD-323; MPN 1N5819WS; LCSC C191023
J15: VALVE C1; TB_DB301V-3.5-2P; MPN DB301V-3.5-2P-GN-S; LCSC C695629
J16: VALVE C2; TB_DB301V-3.5-2P; MPN DB301V-3.5-2P-GN-S; LCSC C695629
J17: VALVE C3; TB_DB301V-3.5-2P; MPN DB301V-3.5-2P-GN-S; LCSC C695629
J18: VALVE WB; TB_DB301V-3.5-2P; MPN DB301V-3.5-2P-GN-S; LCSC C695629
J19: VALVE WASTE; TB_DB301V-3.5-2P; MPN DB301V-3.5-2P-GN-S; LCSC C695629
J20: VALVE INLET; TB_DB301V-3.5-2P; MPN DB301V-3.5-2P-GN-S; LCSC C695629
J21: SPARE OUT 1; TB_DB301V-3.5-2P; MPN DB301V-3.5-2P-GN-S; LCSC C695629
J22: SPARE OUT 2; TB_DB301V-3.5-2P; MPN DB301V-3.5-2P-GN-S; LCSC C695629
J23: HEATER 1; TB_WJ500V-5.08-2P; MPN WJ500V-5.08-2P; LCSC C8465
J24: HEATER 2; TB_WJ500V-5.08-2P; MPN WJ500V-5.08-2P; LCSC C8465
J30: GPIO SPARE; PinHeader_1x09_P2.54mm_Vertical; MPN PZ254V-11-09P; LCSC C492408
Q1, Q2, Q3, Q4, Q5, Q6, Q7, Q8: AO3400A; SOT-23; MPN AO3400A; LCSC C20917
Q9, Q10: AOD4184A; TO-252-2; MPN AOD4184A; LCSC C99124
R31, R32, R33, R34, R35, R36, R37, R38: 100R; R_0603_1608Metric; MPN 0603 100R 1%; LCSC C22775
R41, R42, R43, R44, R45, R46, R47, R48, R61, R62: 100k; R_0603_1608Metric; MPN 0603 100k 1%; LCSC C25803
R51, R52, R53, R54, R55, R56, R57, R58, R67, R68: 4.7k; R_0603_1608Metric; MPN 0603 4.7k 1%; LCSC C23162
R63, R65: 10R; R_0603_1608Metric; MPN 0603 10R 1%; LCSC C22859
R64, R66: 10k; R_0603_1608Metric; MPN 0603 10k 1%; LCSC C25804
R97, R98, R99, R100, R101, R102: 1k; R_0603_1608Metric; MPN 0603 1k 1%; LCSC C21190
U5: UCC27524D; SOIC-8_3.9x4.9mm_P1.27mm; MPN UCC27524DR; LCSC C465729

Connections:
+3V3: D47.1 (K), D48.1 (K), D49.1 (K), D50.1 (K), D51.1 (K), D52.1 (K), J30.7; also elsewhere on the board
+5V_AUX: J30.8; also elsewhere on the board
+12V: C40.1, C41.1, D21.1 (K), D22.1 (K), D23.1 (K), D24.1 (K), D25.1 (K), D26.1 (K), D27.1 (K), D28.1 (K), J15.1, J16.1, J17.1, J18.1, J19.1, J20.1, J21.1, J22.1, R51.1, R52.1, R53.1, R54.1, R55.1, R56.1, R57.1, R58.1, U5.6 (V_{DD}); also elsewhere on the board
+12V_H1: D41.1 (K), J23.2; also elsewhere on the board
+12V_H2: D42.1 (K), J24.2; also elsewhere on the board
GND: C40.2, C41.2, D43.1 (K), D44.1 (K), J30.9, Q1.2 (S), Q2.2 (S), Q3.2 (S), Q4.2 (S), Q5.2 (S), Q6.2 (S), Q7.2 (S), Q8.2 (S), Q9.3 (S), Q10.3 (S), R41.2, R42.2, R43.2, R44.2, R45.2, R46.2, R47.2, R48.2, R61.2, R62.2, R64.2, R66.2, U5.3 (GND); also elsewhere on the board
HEAT1_CMD: R61.1, U5.2 (INA); also elsewhere on the board
HEAT1_DRV: R63.1, R67.1, U5.7 (OUTA)
HEAT1_G: Q9.1 (G), R63.2, R64.1
HEAT1_LED: D43.2 (A), R67.2
HEAT1_N: D41.2 (A), J23.1, Q9.2 (D)
HEAT2_CMD: R62.1, U5.4 (INB); also elsewhere on the board
HEAT2_DRV: R65.1, R68.1, U5.5 (OUTB)
HEAT2_G: Q10.1 (G), R65.2, R66.1
HEAT2_LED: D44.2 (A), R68.2
HEAT2_N: D42.2 (A), J24.1, Q10.2 (D)
MCP_B0: R97.1; also elsewhere on the board
MCP_B1: R98.1; also elsewhere on the board
MCP_B2: R99.1; also elsewhere on the board
MCP_B3: R100.1; also elsewhere on the board
MCP_B4: R101.1; also elsewhere on the board
MCP_B5: R102.1; also elsewhere on the board
SPB0_IO: D47.2 (A), J30.1, R97.2
SPB1_IO: D48.2 (A), J30.2, R98.2
SPB2_IO: D49.2 (A), J30.3, R99.2
SPB3_IO: D50.2 (A), J30.4, R100.2
SPB4_IO: D51.2 (A), J30.5, R101.2
SPB5_IO: D52.2 (A), J30.6, R102.2
VLV1_G: Q1.1 (G), R31.2, R41.1
VLV1_LED: D31.2 (A), R51.2
VLV1_N: D21.2 (A), D31.1 (K), J15.2, Q1.3 (D)
VLV2_G: Q2.1 (G), R32.2, R42.1
VLV2_LED: D32.2 (A), R52.2
VLV2_N: D22.2 (A), D32.1 (K), J16.2, Q2.3 (D)
VLV3_G: Q3.1 (G), R33.2, R43.1
VLV3_LED: D33.2 (A), R53.2
VLV3_N: D23.2 (A), D33.1 (K), J17.2, Q3.3 (D)
VLV4_G: Q4.1 (G), R34.2, R44.1
VLV4_LED: D34.2 (A), R54.2
VLV4_N: D24.2 (A), D34.1 (K), J18.2, Q4.3 (D)
VLV5_G: Q5.1 (G), R35.2, R45.1
VLV5_LED: D35.2 (A), R55.2
VLV5_N: D25.2 (A), D35.1 (K), J19.2, Q5.3 (D)
VLV6_G: Q6.1 (G), R36.2, R46.1
VLV6_LED: D36.2 (A), R56.2
VLV6_N: D26.2 (A), D36.1 (K), J20.2, Q6.3 (D)
VLV7_G: Q7.1 (G), R37.2, R47.1
VLV7_LED: D37.2 (A), R57.2
VLV7_N: D27.2 (A), D37.1 (K), J21.2, Q7.3 (D)
VLV8_G: Q8.1 (G), R38.2, R48.1
VLV8_LED: D38.2 (A), R58.2
VLV8_N: D28.2 (A), D38.1 (K), J22.2, Q8.3 (D)
VLV_C1: R31.1; also elsewhere on the board
VLV_C2: R32.1; also elsewhere on the board
VLV_C3: R33.1; also elsewhere on the board
VLV_INLET: R36.1; also elsewhere on the board
VLV_SP1: R37.1; also elsewhere on the board
VLV_SP2: R38.1; also elsewhere on the board
VLV_WASTE: R35.1; also elsewhere on the board
VLV_WB: R34.1; also elsewhere on the board

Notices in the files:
README.md:
License:
Private project. All rights reserved.
